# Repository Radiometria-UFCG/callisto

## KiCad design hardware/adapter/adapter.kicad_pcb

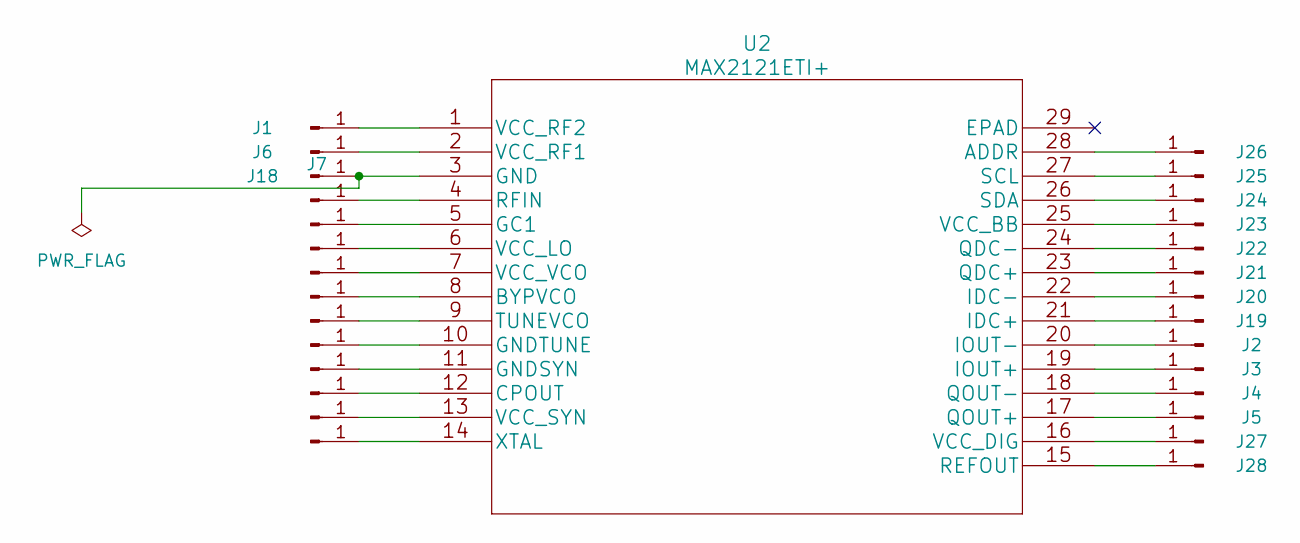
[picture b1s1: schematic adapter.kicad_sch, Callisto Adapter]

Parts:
J1, J2, J3, J4, J5, J6, J7, J8, J9, J10, J11, J12, J13, J14, J15, J16, J17, J18, J19, J20, J21, J22, J23, J24, J25, J26, J27, J28: Conn_01x01_Pin; PinHeader_1x01_P2.54mm_Vertical
U2: MAX2121ETI+; MAX2121ETI&plus_

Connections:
unnamed: J18.1, U2.3 (GND)
unnamed: J1.1, U2.1 (VCC_RF2)
unnamed: J2.1, U2.20 (IOUT-)
unnamed: J3.1, U2.19 (IOUT+)
unnamed: J4.1, U2.18 (QOUT-)
unnamed: J5.1, U2.17 (QOUT+)
unnamed: J6.1, U2.2 (VCC_RF1)
unnamed: J7.1, U2.4 (RFIN)
unnamed: J8.1, U2.5 (GC1)
unnamed: J9.1, U2.6 (VCC_LO)
unnamed: J10.1, U2.7 (VCC_VCO)
unnamed: J11.1, U2.8 (BYPVCO)
unnamed: J12.1, U2.9 (TUNEVCO)
unnamed: J13.1, U2.10 (GNDTUNE)
unnamed: J14.1, U2.12 (CPOUT)
unnamed: J15.1, U2.13 (VCC_SYN)
unnamed: J16.1, U2.14 (XTAL)
unnamed: J17.1, U2.11 (GNDSYN)
unnamed: J19.1, U2.21 (IDC+)
unnamed: J20.1, U2.22 (IDC-)
unnamed: J21.1, U2.23 (QDC+)
unnamed: J22.1, U2.24 (QDC-)
unnamed: J23.1, U2.25 (VCC_BB)
unnamed: J24.1, U2.26 (SDA)
unnamed: J25.1, U2.27 (SCL)
unnamed: J26.1, U2.28 (ADDR)
unnamed: J27.1, U2.16 (VCC_DIG)
unnamed: J28.1, U2.15 (REFOUT)

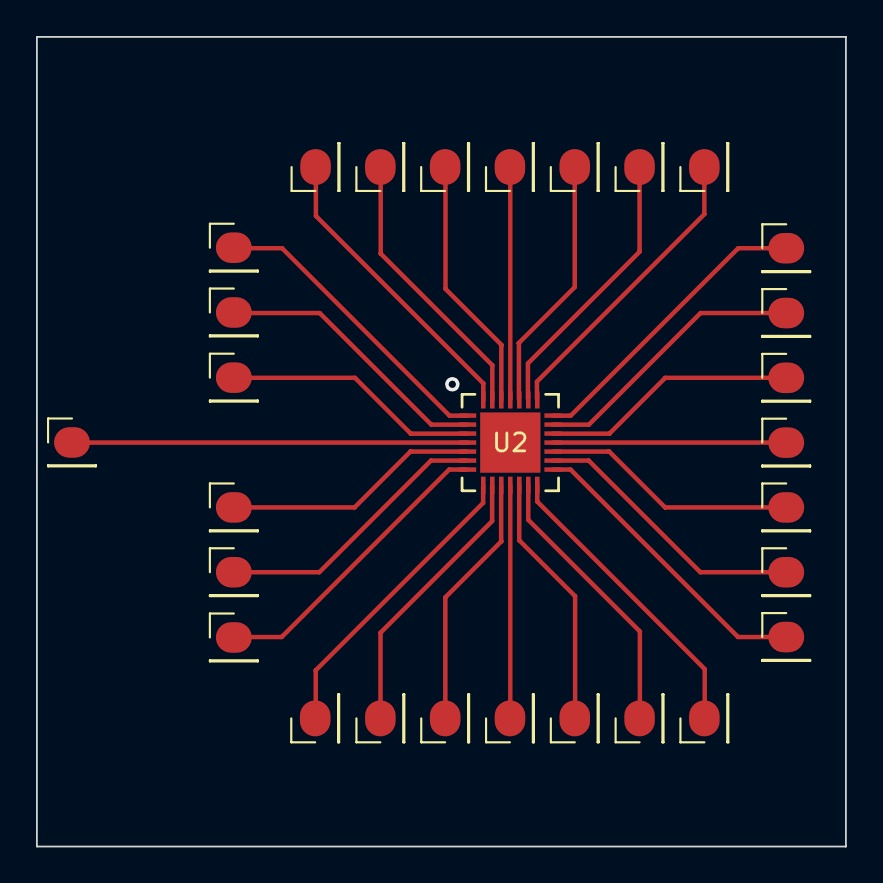
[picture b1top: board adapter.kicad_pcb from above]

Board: 2 copper layers, 44.9 x 45.0 mm, 29 parts (0 on the bottom side), 28 nets.

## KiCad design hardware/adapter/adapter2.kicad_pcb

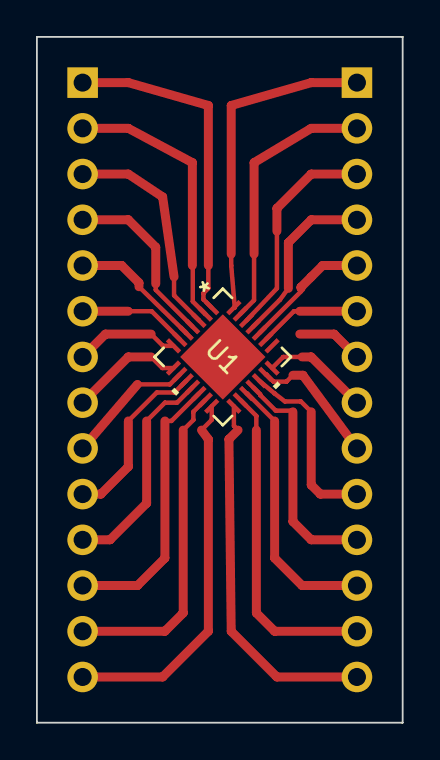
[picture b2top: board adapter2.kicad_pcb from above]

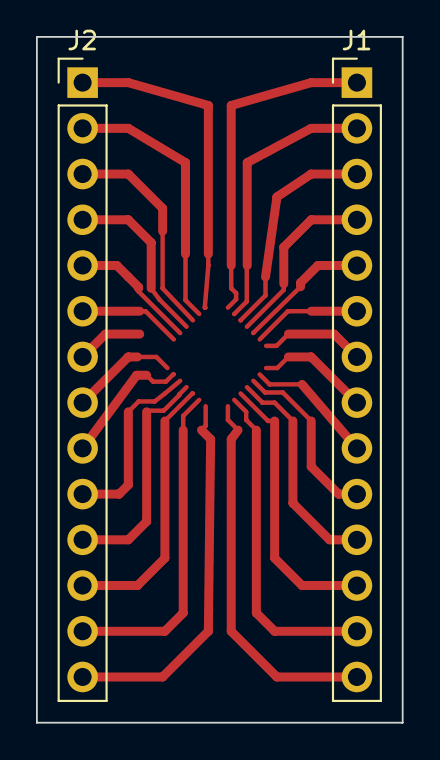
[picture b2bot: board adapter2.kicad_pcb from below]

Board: 2 copper layers, 20.3 x 38.1 mm, 3 parts (2 on the bottom side), 28 nets.

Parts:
J1, J2: Conn_01x14_Pin; PinHeader_1x14_P2.54mm_Vertical
U1: MAX2121ETI+; 21-0140L_T2855-3_MXM

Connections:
unnamed: J1.1, U1.1 (VCC_RF2)
unnamed: J1.2, U1.2 (VCC_RF1)
unnamed: J1.3, U1.3 (GND)
unnamed: J1.4, U1.4 (RFIN)
unnamed: J1.5, U1.5 (GC1)
unnamed: J1.6, U1.6 (VCC_LO)
unnamed: J1.7, U1.7 (VCC_VCO)
unnamed: J1.8, U1.8 (BYPVCO)
unnamed: J1.9, U1.9 (TUNEVCO)
unnamed: J1.10, U1.10 (GNDTUNE)
unnamed: J1.11, U1.11 (GNDSYN)
unnamed: J1.12, U1.12 (CPOUT)
unnamed: J1.13, U1.13 (VCC_SYN)
unnamed: J1.14, U1.14 (XTAL)
unnamed: J2.1, U1.28 (ADDR)
unnamed: J2.2, U1.27 (SCL)
unnamed: J2.3, U1.26 (SDA)
unnamed: J2.4, U1.25 (VCC_BB)
unnamed: J2.5, U1.24 (QDC-)
unnamed: J2.6, U1.23 (QDC+)
unnamed: J2.7, U1.22 (IDC-)
unnamed: J2.8, U1.21 (IDC+)
unnamed: J2.9, U1.20 (IOUT-)
unnamed: J2.10, U1.19 (IOUT+)
unnamed: J2.11, U1.18 (QOUT-)
unnamed: J2.12, U1.17 (QOUT+)
unnamed: J2.13, U1.16 (VCC_DIG)
unnamed: J2.14, U1.15 (REFOUT)

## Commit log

2023-05-04 change README
2023-05-15 change gitignore
2023-05-15 create adapter project
2023-05-19 Create Arquivos pdf callisto
2023-06-06 fix connector
2023-06-06 fix net
2023-06-06 fix chip pads
2023-06-06 new space offset

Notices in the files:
parts and their libraries:
Copyright 2016 Accelerated Designs. All rights reserved.
